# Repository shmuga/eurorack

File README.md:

# Eurorack modules

1. [multbuf](./multbuf/README.md) - Dual buffered multiple

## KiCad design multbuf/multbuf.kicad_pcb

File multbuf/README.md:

# multbuf

A simple dual buffered multiple module with LED indicating the polarity of the input signal, printed with panel. Make sure to remove order number.

Schema file: [link](./multbuf.pdf)
PCB ready for pinting: [link]('./pcb.zip') 

## PCB

Pcb is fully through hole and easy to solder. Note that power connector should be soldered from the other side

## BOM

| Reference          | Value | Qty | Comment                    |
|--------------------|-------|-----|----------------------------|
| C1,C2              | 10uf  | 2   | 35V Electrolytic capacitor |
| C3,C4,C5,C6        | 100nf | 4   |                            |
| D1                 | LED1  | 1   | bipolar LED                |
| D2                 | LED2  | 1   | bipolar LED                |
| J1                 | POWER | 1   | 2x5 POWER Connctor         |
| J2                 | IN1   | 1   | Thonkiconn - 3.5mm Jack    |
| J3                 | OUT11 | 1   | Thonkiconn - 3.5mm Jack    |
| J4                 | OUT12 | 1   | Thonkiconn - 3.5mm Jack    |
| J5                 | OUT13 | 1   | Thonkiconn - 3.5mm Jack    |
| J6                 | IN2   | 1   | Thonkiconn - 3.5mm Jack    |
| J7                 | OUT21 | 1   | Thonkiconn - 3.5mm Jack    |
| J8                 | OUT22 | 1   | Thonkiconn - 3.5mm Jack    |
| J9                 | OUT23 | 1   | Thonkiconn - 3.5mm Jack    |
| R1,R6              | 100K  | 2   | 1/4 W                      |
| R2,R7              | 330   | 2   | 1/4 W                      |
| R3,R4,R5,R8,R9,R10 | 1K    | 6   | 1/4 W                      |
| U1,U2              | TL074 | 2   |                            |

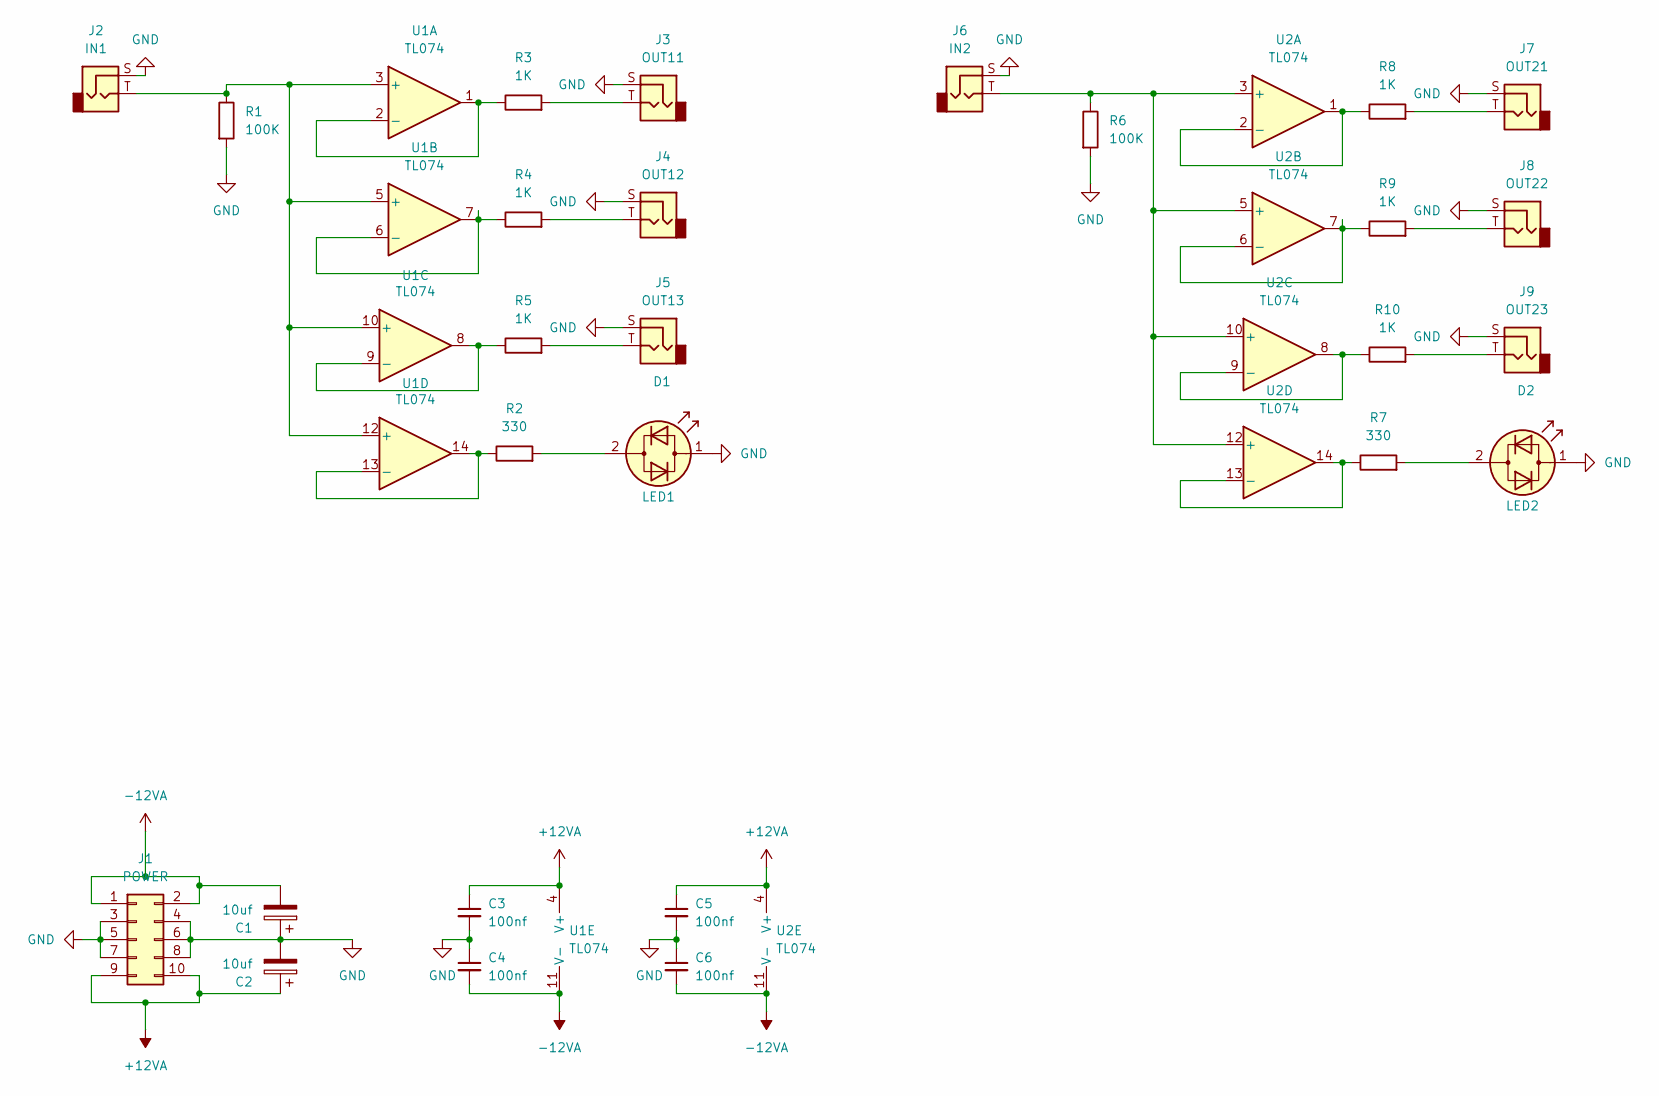
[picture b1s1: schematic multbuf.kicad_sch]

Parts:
C1, C2: 10uf; CP_Radial_Tantal_D5.0mm_P2.50mm
C3, C4, C5, C6: 100nf; C_Disc_D5.0mm_W2.5mm_P5.00mm
D1: LED1; LED_D3.0mm_Clear
D2: LED2; LED_D3.0mm_Clear
J1: POWER; IDC-Header_2x05_P2.54mm_Vertical
J2: IN1; Jack_3.5mm_QingPu_WQP-PJ398SM_Vertical_CircularHoles
J3: OUT11; Jack_3.5mm_QingPu_WQP-PJ398SM_Vertical_CircularHoles
J4: OUT12; Jack_3.5mm_QingPu_WQP-PJ398SM_Vertical_CircularHoles
J5: OUT13; Jack_3.5mm_QingPu_WQP-PJ398SM_Vertical_CircularHoles
J6: IN2; Jack_3.5mm_QingPu_WQP-PJ398SM_Vertical_CircularHoles
J7: OUT21; Jack_3.5mm_QingPu_WQP-PJ398SM_Vertical_CircularHoles
J8: OUT22; Jack_3.5mm_QingPu_WQP-PJ398SM_Vertical_CircularHoles
J9: OUT23; Jack_3.5mm_QingPu_WQP-PJ398SM_Vertical_CircularHoles
R1, R6: 100K; R_Axial_DIN0207_L6.3mm_D2.5mm_P10.16mm_Horizontal
R2, R7: 330; R_Axial_DIN0207_L6.3mm_D2.5mm_P10.16mm_Horizontal
R3, R4, R5, R8, R9, R10: 1K; R_Axial_DIN0207_L6.3mm_D2.5mm_P10.16mm_Horizontal
U1, U2: TL074; DIP-14_W7.62mm

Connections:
+12VA: C2.1, C3.1, C5.1, J1.9, J1.10, U1.4 (V+), U2.4 (V+)
-12VA: C1.2, C4.2, C6.2, J1.1, J1.2, U1.11 (V-), U2.11 (V-)
GND: C1.1, C2.2, C3.2, C4.1, C5.2, C6.1, D1.1 (KA), D2.1 (KA), J1.3, J1.4, J1.5, J1.6, J1.7, J1.8, J2.S, J3.S, J4.S, J5.S, J6.S, J7.S, J8.S, J9.S, R1.2, R6.2; also elsewhere on the board
unnamed: D1.2 (AK), R2.2
unnamed: D2.2 (AK), R7.2
unnamed: J3.T, R3.2
unnamed: J4.T, R4.2
unnamed: J5.T, R5.2
unnamed: J7.T, R8.2
unnamed: J8.T, R9.2
unnamed: J9.T, R10.2
unnamed: J2.T, R1.1, U1.3 (+), U1.5 (+), U1.10 (+), U1.12 (+)
unnamed: R3.1, U1.1, U1.2 (-)
unnamed: R4.1, U1.6 (-), U1.7
unnamed: R5.1, U1.8, U1.9 (-)
unnamed: R2.1, U1.13 (-), U1.14
unnamed: J6.T, R6.1, U2.3 (+), U2.5 (+), U2.10 (+), U2.12 (+)
unnamed: R8.1, U2.1, U2.2 (-)
unnamed: R9.1, U2.6 (-), U2.7
unnamed: R10.1, U2.8, U2.9 (-)
unnamed: R7.1, U2.13 (-), U2.14

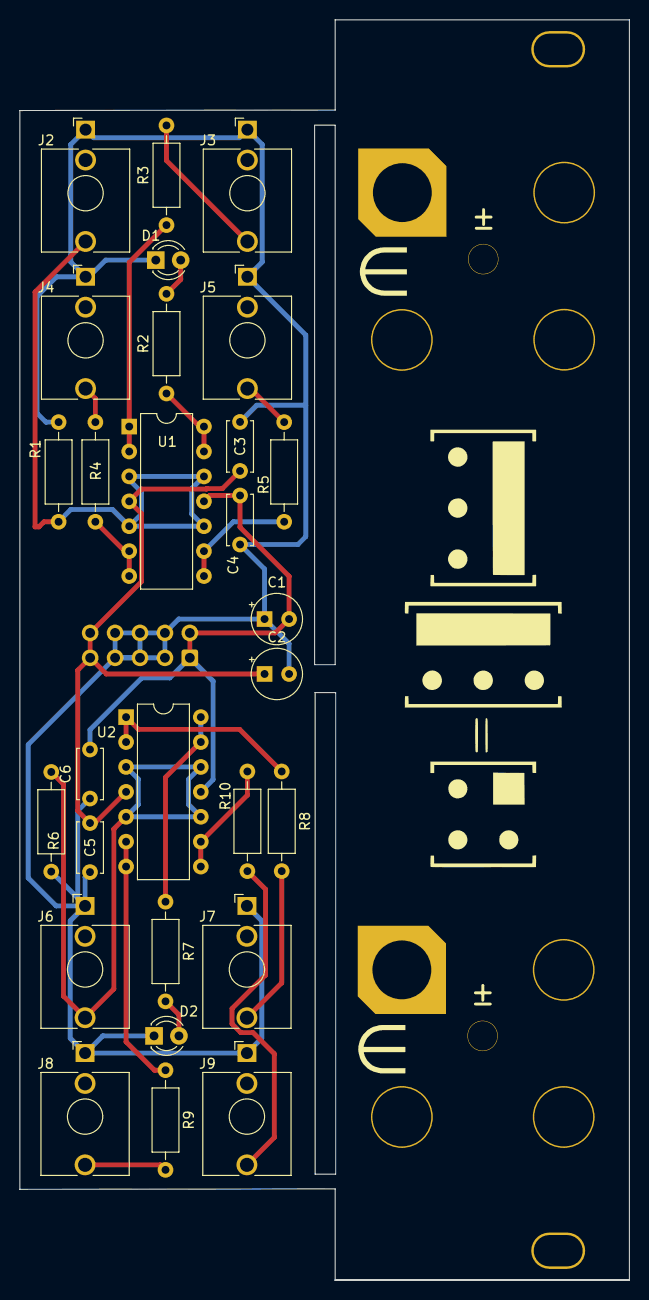
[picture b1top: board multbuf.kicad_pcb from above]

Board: 2 copper layers, 62.2 x 128.5 mm, 39 parts (1 on the bottom side), 21 nets.

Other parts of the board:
D1Hp: led1p; LED_D3.0mm_Clear_PANEL
D1Hp#2: LED1p; LED_D3.0mm_Clear_PANEL
JJ1, JJ1#2: IN1; Jack_3.5mm_QingPu_WQP-PJ398SM_PANEL
JJ2, JJ2#2: OUT11; Jack_3.5mm_QingPu_WQP-PJ398SM_PANEL
JJ3, JJ3#2: OUT12; Jack_3.5mm_QingPu_WQP-PJ398SM_PANEL
JJ4, JJ4#2: OUT13; Jack_3.5mm_QingPu_WQP-PJ398SM_PANEL

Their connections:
GND: D1Hp.1 (KA), D1Hp#2.1 (KA); also elsewhere on the board

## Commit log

2025-01-26 feat(multbuf): Adds buffered multiple
2025-01-26 chore: more multbuf docs
